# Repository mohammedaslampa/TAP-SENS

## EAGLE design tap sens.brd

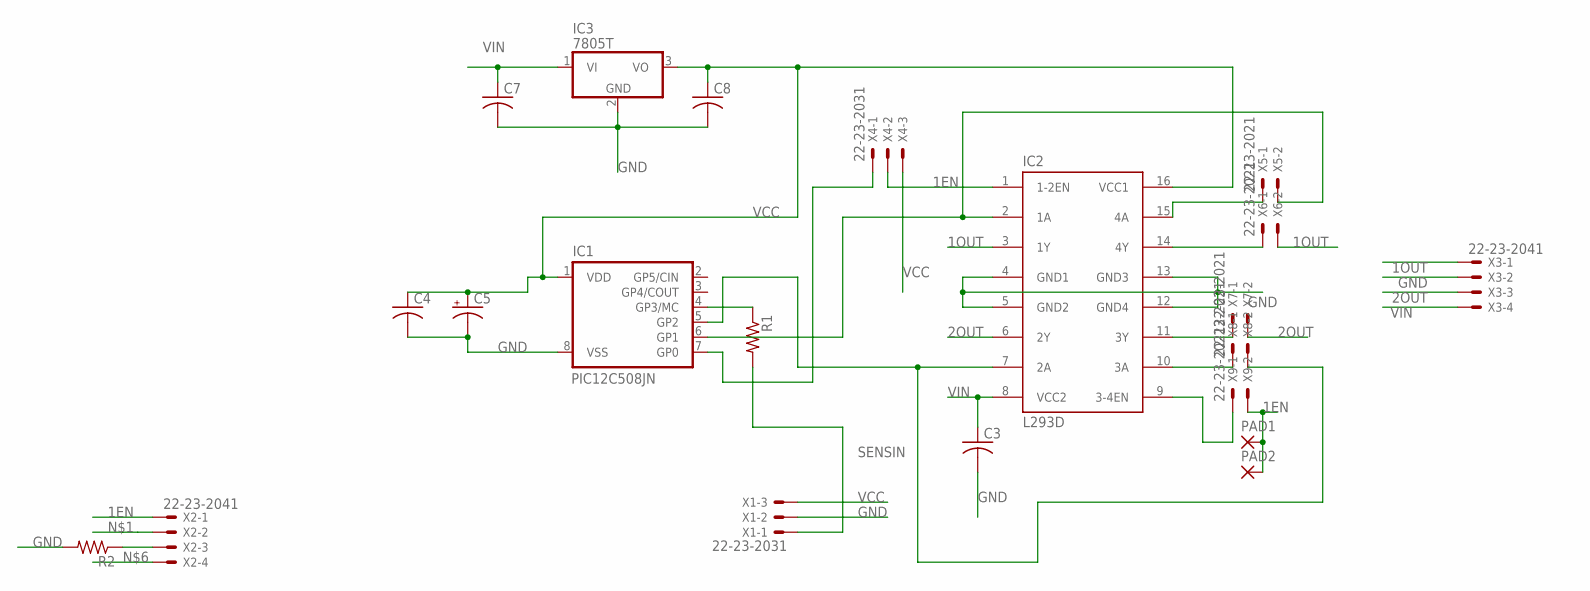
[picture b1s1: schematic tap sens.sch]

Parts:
C3, C4, C7, C8: C-US050-025X075; C050-025X075
C5: CPOL-USE5-8.5; E5-8,5
IC1: PIC12C508JN; DIL8
IC2: L293D; DIL16
IC3: 7805T; TO220H
PAD1, PAD2: 2,54/0,8
R1, R2: R-US_0207/10; 0207/10
X1, X4: 22-23-2031
X2, X3: 22-23-2041
X5, X6, X7, X8, X9: 22-23-2021

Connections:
1EN: IC2.1 (1-2EN), PAD1.1, PAD2.1, X2.1, X4.2, X9.2
1OUT: IC2.3 (1Y), X3.1, X6.2
2OUT: IC2.6 (2Y), X3.3, X7.2
GND: C3.2, C4.2, C5.-, C7.2, C8.2, IC1.8 (VSS), IC2.4 (GND1), IC2.5 (GND2), IC2.12 (GND4), IC2.13 (GND3), IC3.2 (GND), R2.2, X1.2, X3.2
unnamed: IC1.6 (GP1), IC2.2 (1A), X2.2, X5.2
unnamed: R2.1, X2.3
unnamed: IC1.4 (GP3/MC), R1.1
unnamed: IC1.5 (GP2), IC2.7 (2A), X2.4, X8.2
unnamed: IC1.7 (GP0), X4.1
unnamed: IC2.9 (3-4EN), X9.1
unnamed: IC2.10 (3A), X8.1
unnamed: IC2.11 (3Y), X7.1
unnamed: IC2.14 (4Y), X6.1
unnamed: IC2.15 (4A), X5.1
SENSIN: R1.2, X1.1
VCC: C4.1, C5.+, C8.1, IC1.1 (VDD), IC2.16 (VCC1), IC3.3 (VO), X1.3, X4.3
VIN: C3.1, C7.1, IC2.8 (VCC2), IC3.1 (VI), X3.4

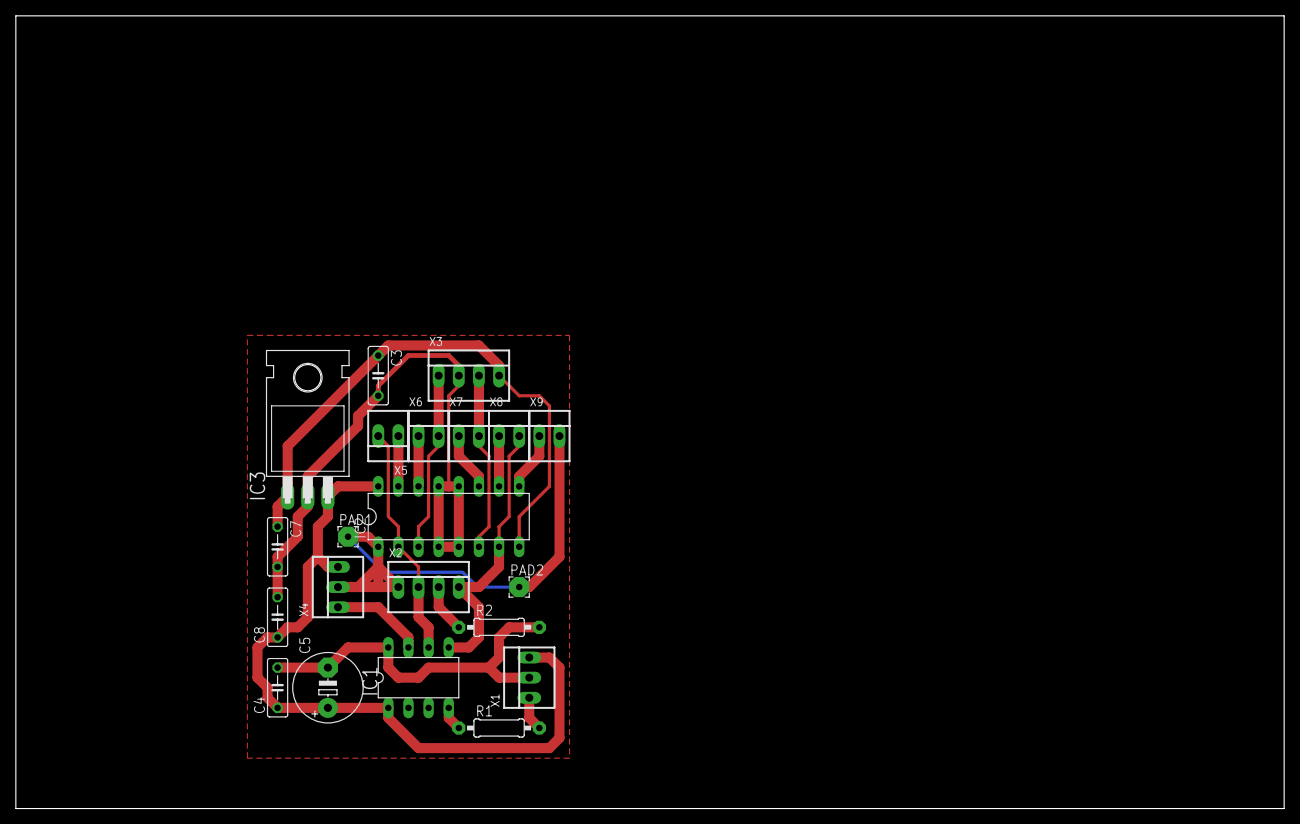
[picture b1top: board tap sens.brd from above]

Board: 2 copper layers, 160.0 x 100.0 mm, 21 parts (0 on the bottom side), 17 nets.

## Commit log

2021-06-06 NEWMAIN.C
    MPLABX V5.45
    MICROCONTROLLER = PIC12F508
    IR PROXIMITY SENSOR = HW-201
    SOLENOID DRIVER = L293D
2021-06-06 SCHEMATIC DIAGRAM
    USING AUTODESK EAGLE
    NEEED TO VERIFY(IN PROTO STAGE)
2021-06-06 PCB LAYOUT
    NEED VERIFICATION
    USING AUTODESK EAGLE
